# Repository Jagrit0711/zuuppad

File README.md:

# Zuup

Zuup is a cicropad is a 9 key macropad built around the Arduino Pro Micro.

## Features
- 9 MX-style mechanical switches in a 3x3 grid  
- xiao-rp2040-dip as the brains  
- circuitpython

## Photos

## CAD Model

in my case the switches and controller are fully visible because it looks cool like tht lol  
for usb c there with a pill shaped cutout. i didn't made top panel i have made the bezzle and i am going to manually cut and place a acrylic sheet so that internal components are always visible hence i didn't made a top panel and my pcb is elevated so it doesnt require a plate

## PCB

i made it on KiCad 10. i used 9 MX_PCB_1.00u switch footprints in a clean 3x3 grid. Diodes are DO-35 1N4148, one per key i also aded random usless cool stuff on the pcb too

## Firmware Overview

Uses circuitpython firmware.  
9 keys act as fully remappable macros

## BOM

- 9x MX-style mechanical switches  
- 9x keycaps (1u)  
- 9x 1N4148 DO-35 diodes  
- 1x xiao-rp2040-dip  
- 3x M2x5mm screws  
- 1x 3D printed open-top tray  
- 1x PCB i made  

## fun stuff

i made a micropad yay!

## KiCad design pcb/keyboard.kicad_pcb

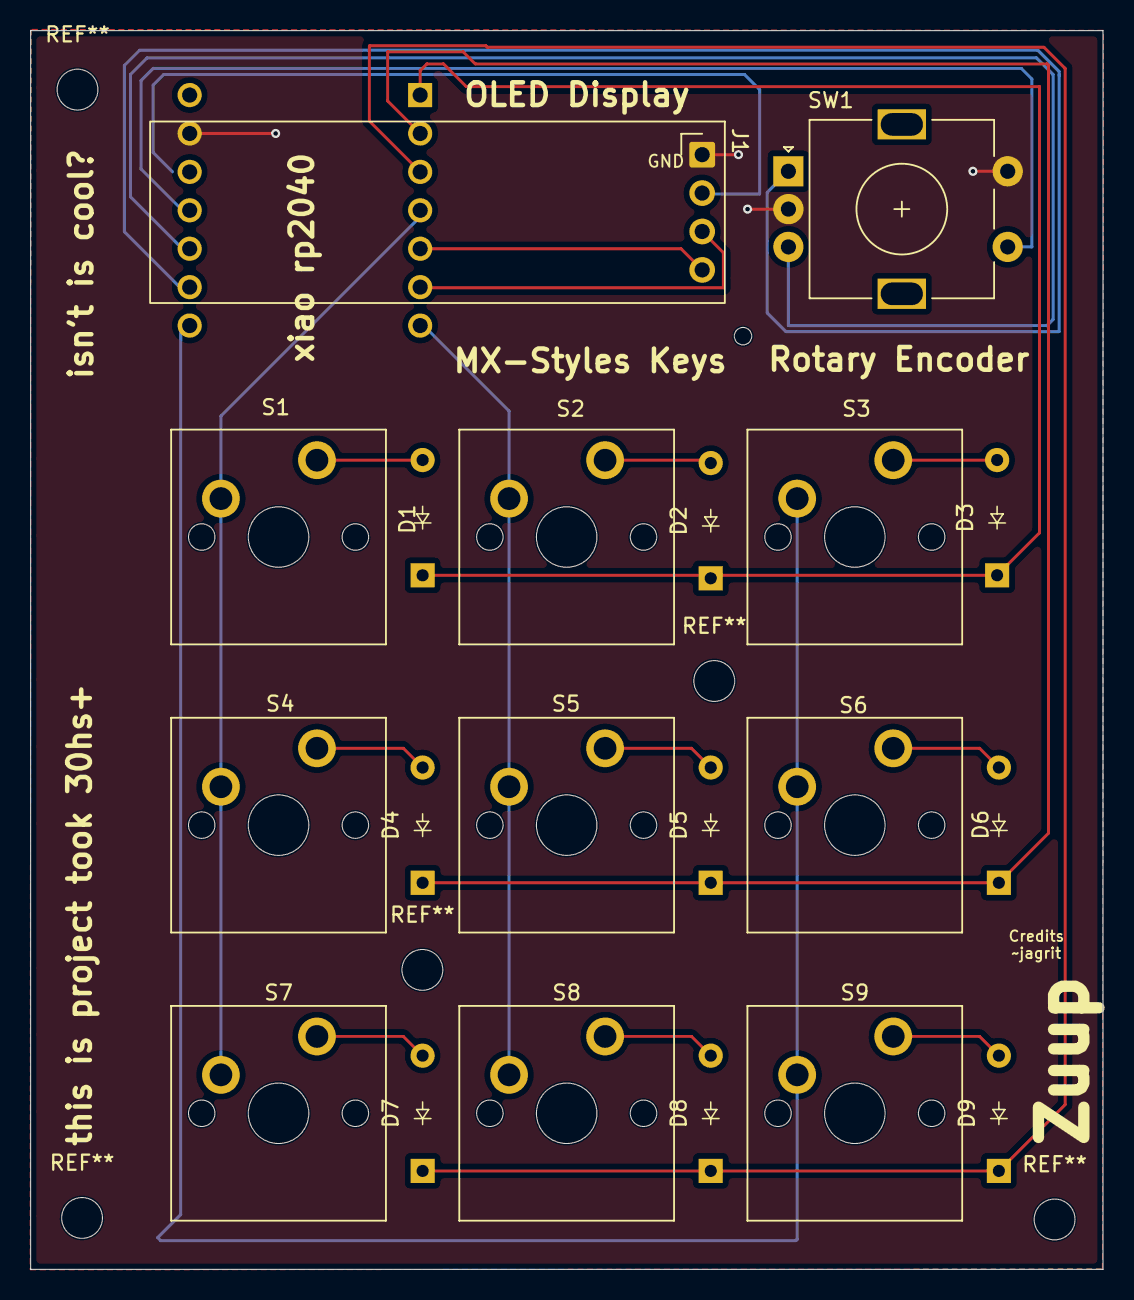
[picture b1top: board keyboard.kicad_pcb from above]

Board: 2 copper layers, 70.9 x 81.9 mm, 21 parts (1 on the bottom side), 22 nets.

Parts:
D1, D2, D3, D4, D5, D6, D7, D8, D9: Diode_DO-35
J1: Conn_01x04_Pin; ER_OLEDM0.91_1x-I2C
S1, S2, S3, S4, S5, S6, S7, S8, S9: MX_PCB_1.00u
SW1: RotaryEncoder_Switch; RotaryEncoder_Alps_EC11E-Switch_Vertical_H20mm
U1: MCU_Seeed_XIAO_RP2040; Seeed_XIAO_RP2040

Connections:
3V3: J1.2, U1.12 (3V3)
ENC_A: SW1.A, U1.9 (PA7_A8_D8_SCK)
ENC_B: SW1.B, U1.10 (PA5_A9_D9_MISO)
ENC_SW: SW1.S1, U1.11 (PA6_A10_D10_MOSI)
GND: J1.1, SW1.C, SW1.S2, U1.13 (GND)
unnamed: D1.2 (A), S1.2
unnamed: D2.2 (A), S2.2
unnamed: D3.2 (A), S3.2
unnamed: D4.2 (A), S4.2
unnamed: D5.2 (A), S5.2
unnamed: D6.2 (A), S6.2
unnamed: D7.2 (A), S7.2
unnamed: D8.2 (A), S8.2
unnamed: D9.2 (A), S9.2
Row 0: D1.1 (K), D2.1 (K), D3.1 (K), U1.1 (PA02_A0_D0)
Row 1: D4.1 (K), D5.1 (K), D6.1 (K), U1.2 (PA4_A1_D1)
Row 2: D7.1 (K), D8.1 (K), D9.1 (K), U1.3 (PA10_A2_D2)
SCL: J1.3, U1.6 (PA9_A5_D5_SCL)
SDA: J1.4, U1.5 (PA8_A4_D4_SDA)
col 0: S1.1, S4.1, S7.1, U1.4 (PA11_A3_D3)
col 1: S2.1, S5.1, S8.1, U1.7 (PB08_A6_D6_TX)
col 2: S3.1, S6.1, S9.1, U1.8 (PB09_A7_D7_RX)

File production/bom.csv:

Designator,Footprint,Quantity,Value,LCSC Part #
"D1, D2, D3, D4, D5, D6, D7, D8, D9",Diode_DO-35,9,~,
J1,ER_OLEDM0.91_1x-I2C,1,Conn_01x04_Pin,
"S1, S2, S3, S4, S5, S6, S7, S8, S9",MX_PCB_1.00u,9,~,
SW1,RotaryEncoder_Alps_EC11E-Switch_Vertical_H20mm,1,RotaryEncoder_Switch,
U1,Seeed_XIAO_RP2040,1,MCU_Seeed_XIAO_RP2040,

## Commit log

2026-03-14 Modified KiCad hardware files
2026-03-14 Change controller from Arduino Pro Micro to Raspberry Pi Pico
    Updated the README to reflect the use of Raspberry Pi Pico instead of Arduino Pro Micro.
2026-03-14 phots fixed
2026-03-14 Update README with new hardware and firmware details
2026-03-14 oled screen a dial new case new pc
2026-03-16 clean repo remove large file
2026-03-16 photos in readme fixed
2026-03-16 added f3d file
2026-03-16 python firmware
2026-03-16 Fix spelling of 'circuitpython' in README
    Corrected spelling of 'circuitpython' in multiple sections.
2026-06-07 firmware push in circuite python and qmk
